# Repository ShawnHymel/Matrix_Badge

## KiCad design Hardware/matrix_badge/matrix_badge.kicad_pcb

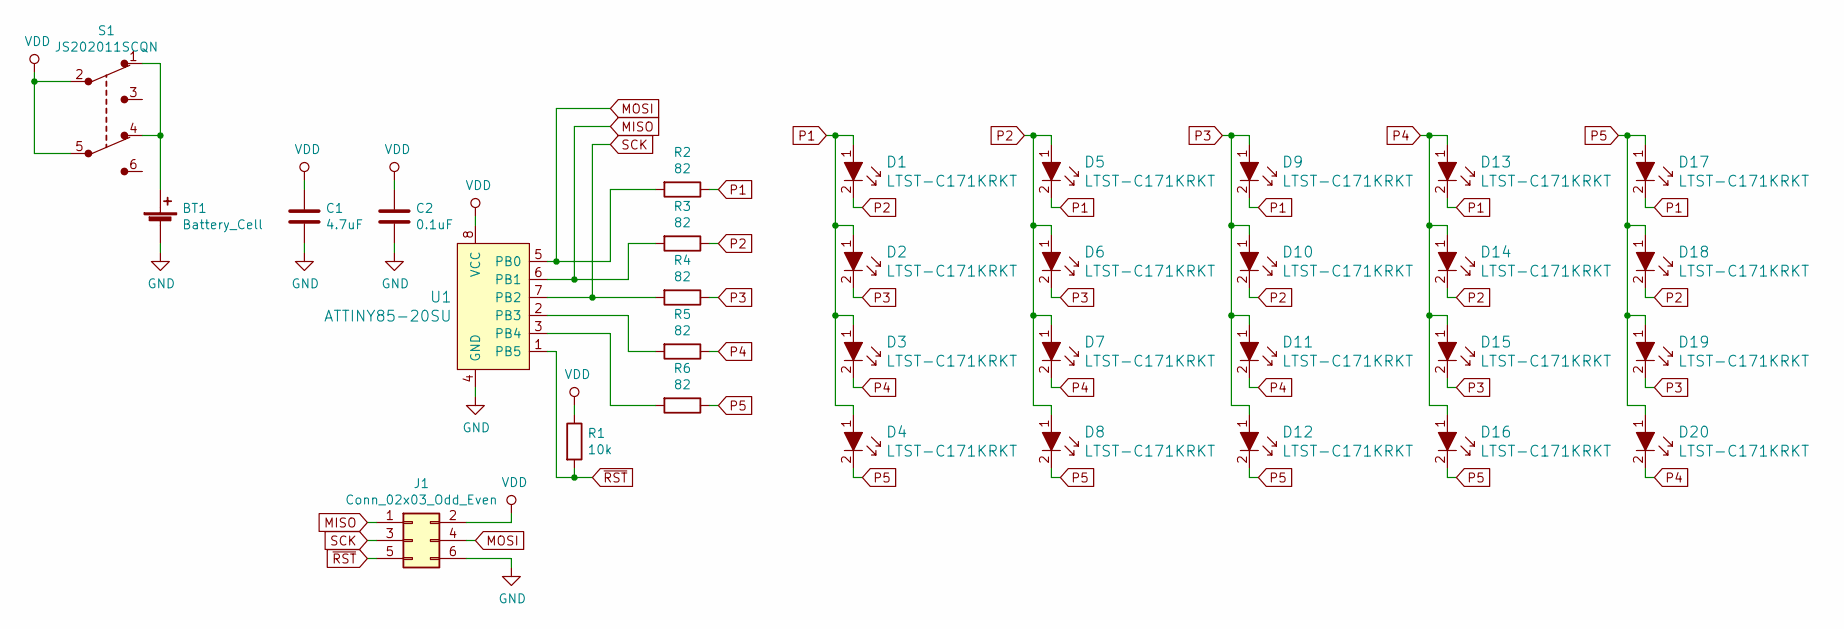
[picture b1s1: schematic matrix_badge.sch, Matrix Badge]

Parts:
BT1: Battery_Cell; BatteryHolder_Keystone_3034_1x20mm
C1: 4.7uF; C_0805_2012Metric_Pad1.15x1.40mm_HandSolder
C2: 0.1uF; C_0805_2012Metric_Pad1.15x1.40mm_HandSolder
D1, D2, D3, D4, D5, D6, D7, D8, D9, D10, D11, D12, D13, D14, D15, D16, D17, D18, D19, D20: LTST-C171KRKT; 0805; MPN LTST-C171KRKT; Digi-Key_PN 160-1427-1-ND
J1: Conn_02x03_Odd_Even; PinSocket_2x03_P2.54mm_Vertical
R1: 10k; R_0805_2012Metric_Pad1.15x1.40mm_HandSolder
R2, R3, R4, R5, R6: 82; R_0805_2012Metric_Pad1.15x1.40mm_HandSolder
S1: JS202011SCQN; Switch_Slide_JS202011SCQN; MPN JS202011SCQN; Digi-Key_PN 401-2002-1-ND
U1: ATTINY85-20SU; SOIJ-8_5.3x5.3mm_P1.27mm; MPN ATTINY85-20SU; Digi-Key_PN ATTINY85-20SU-ND

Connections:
GND: BT1.2 (-), C1.2, C2.2, J1.6, U1.4 (GND)
MISO: J1.1, R3.2, U1.6 (PB1)
MOSI: J1.4, R2.2, U1.5 (PB0)
unnamed: BT1.1 (+), S1.1, S1.4
unnamed: R5.2, U1.2 (PB3)
unnamed: R6.2, U1.3 (PB4)
P1: D1.1, D2.1, D3.1, D4.1, D5.2, D9.2, D13.2, D17.2, R2.1
P2: D1.2, D5.1, D6.1, D7.1, D8.1, D10.2, D14.2, D18.2, R3.1
P3: D2.2, D6.2, D9.1, D10.1, D11.1, D12.1, D15.2, D19.2, R4.1
P4: D3.2, D7.2, D11.2, D13.1, D14.1, D15.1, D16.1, D20.2, R5.1
P5: D4.2, D8.2, D12.2, D16.2, D17.1, D18.1, D19.1, D20.1, R6.1
SCK: J1.3, R4.2, U1.7 (PB2)
VDD: C1.1, C2.1, J1.2, R1.1, S1.2, S1.5, U1.8 (VCC)
~RST: J1.5, R1.2, U1.1 (PB5)

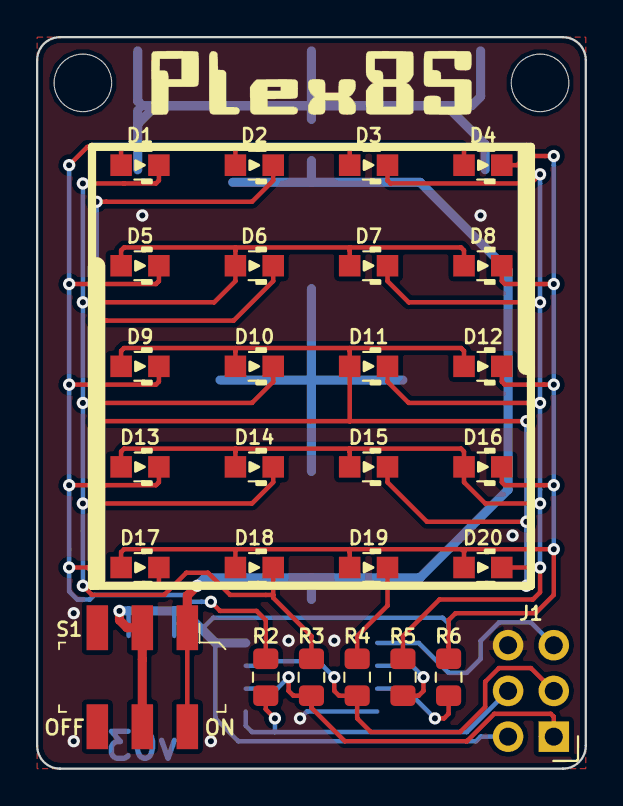
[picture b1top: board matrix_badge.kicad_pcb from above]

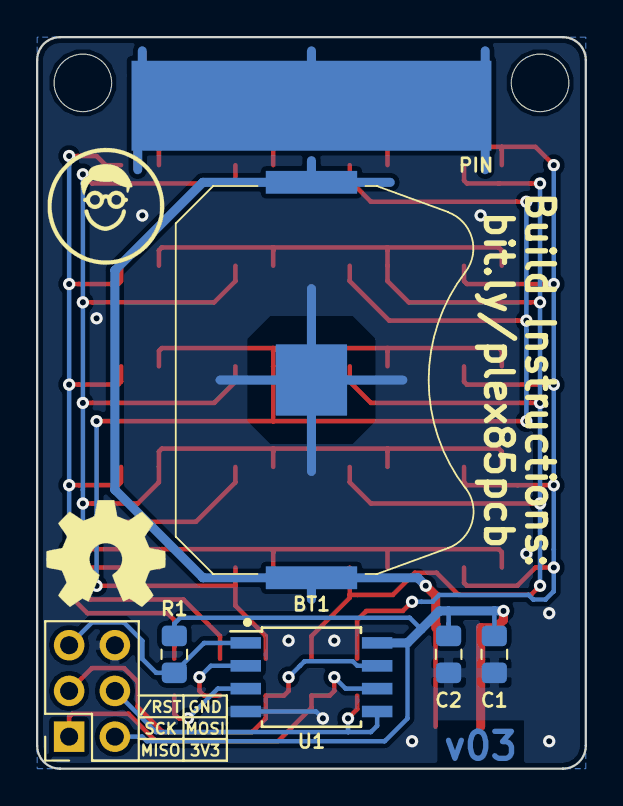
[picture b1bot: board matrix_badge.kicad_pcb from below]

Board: 2 copper layers, 30.5 x 40.6 mm, 33 parts (7 on the bottom side), 14 nets.

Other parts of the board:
PIN: pin_safety_sq_20mm

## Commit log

2019-01-31 Parts moved into initial spots
2019-01-31 Reconfigured footprint positions
2019-01-31 Updated .gitignore file
2019-02-01 Layout ALMOST done. Missing 1 gnd connection.
2019-02-01 Finally got that last stupid #$%@# trace
2019-02-01 Added basic silkscreen
2019-02-01 Added pretty silkscreen. Well, pretty by my standards.
2019-02-02 Ran gerbers and made BOM
2019-02-05 Updated BOM with battery.
2019-03-03 Made fixes for v02 (added wide body SOIC and swapped round pin for rectangular pin back). Added ON/OFF silk for v03.
2019-03-20 Added ATtiny85 datasheet and blinky sketch.

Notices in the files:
Hardware/matrix_badge/matrix_badge.sch:
creativecommons.org/licenses/by/4.0
License: CC BY 4.0
